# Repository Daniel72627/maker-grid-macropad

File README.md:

# The Maker Grid Macropad

The Maker Grid Macropad is a 9-key macropad with a rotary encoder and an OLED Display. It uses KMK firmware on a Seeed XIAO RP2040. 

It serves as a dedicated hardware tool to make designing custom robotics chassis, brackets, and mechanisms in CAD much more efficient!

## Features:
* 3D printed sandwich-style case. looks awesome doesn't it??
* 128x32 OLED Display to show active tool layers
* EC11 Rotary encoder for zooming and panning across the canvas
* 9 Keys for all my most-used CAD shortcuts

## CAD Model:

Everything fits together using M3 Bolts and heatset inserts. 
It has 2 separate 3D printed pieces. The bottom shell where the PCB sits, and the top plate with the cutouts for the switches. 

Made in Fusion360. Nifty

## PCB
Here's my PCB! It was made in KiCad. 

### Schematic

### PCB

I used a COL2ROW diode matrix for the keyswitch footprints to prevent ghosting. I think in retrospect, routing the I2C traces for the OLED was the trickiest part. 

## Firmware Overview
This hackpad uses KMK firmware (CircuitPython) for everything.

* The rotary encoder zooms in and out on the canvas. 
* The 9 keys currently act as macros for my most used Fusion 360 tools, dynamically changing based on whether I am Sketching, Solid Modeling, or Assembling.
* The OLED displays exactly which layer I am currently on!

I might add more in the future! That's it for now

## BOM:
Here should be everything you need to make this hackpad

* 9x Cherry MX-style Switches
* 9x Blank DSA Keycaps
* M3 Heat-Set Inserts & M3 Socket Cap Screws
* 9x 1N4148 Through-hole Diodes
* 1x 0.91" 128x32 OLED Display
* 1x EC11 Rotary Encoder + Knob
* 1x XIAO RP2040
* 1x Case (2 3D printed parts)

## Extra stuff
Oh fun fact: I designed this specifically because clicking through menus while designing our base robot for FTC Team 7082 was taking way too long LOL

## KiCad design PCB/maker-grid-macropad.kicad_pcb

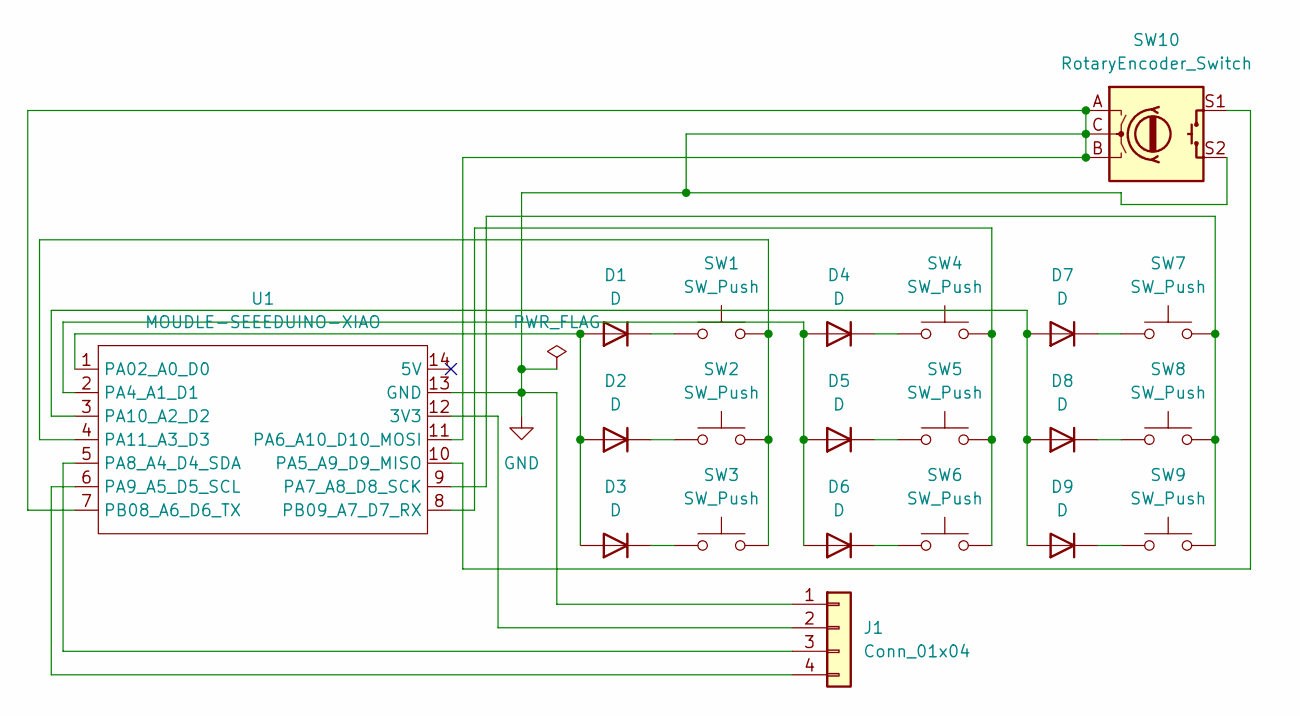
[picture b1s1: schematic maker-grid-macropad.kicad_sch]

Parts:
D1, D2, D3, D4, D5, D6, D7, D8, D9: D; D_DO-35_SOD27_P7.62mm_Horizontal
J1: Conn_01x04; PinHeader_1x04_P2.54mm_Vertical
SW1, SW2, SW3, SW4, SW5, SW6, SW7, SW8, SW9: SW_Push; SW_Cherry_MX_1.00u_PCB
SW10: RotaryEncoder_Switch; RotaryEncoder_Alps_EC11E-Switch_Vertical_H20mm
U1: MOUDLE-SEEEDUINO-XIAO; XIAO-Generic-Hybrid-14P-2.54-21X17.8MM

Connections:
GND: J1.1, SW10.A, SW10.B, SW10.C, SW10.S2, U1.7 (PB08_A6_D6_TX), U1.11 (PA6_A10_D10_MOSI), U1.13 (GND)
unnamed: D1.2 (A), D2.2 (A), D3.2 (A), U1.1 (PA02_A0_D0)
unnamed: D1.1 (K), SW1.1
unnamed: D2.1 (K), SW2.1
unnamed: D3.1 (K), SW3.1
unnamed: D4.2 (A), D5.2 (A), D6.2 (A), U1.2 (PA4_A1_D1)
unnamed: D4.1 (K), SW4.1
unnamed: D5.1 (K), SW5.1
unnamed: D6.1 (K), SW6.1
unnamed: D7.2 (A), D8.2 (A), D9.2 (A), U1.3 (PA10_A2_D2)
unnamed: D7.1 (K), SW7.1
unnamed: D8.1 (K), SW8.1
unnamed: D9.1 (K), SW9.1
unnamed: J1.2, U1.12 (3V3)
unnamed: J1.3, U1.5 (PA8_A4_D4_SDA)
unnamed: J1.4, U1.6 (PA9_A5_D5_SCL)
unnamed: SW10.S1, U1.10 (PA5_A9_D9_MISO)
unnamed: SW7.2, SW8.2, SW9.2, U1.9 (PA7_A8_D8_SCK)
unnamed: SW1.2, SW2.2, SW3.2, U1.4 (PA11_A3_D3)
unnamed: SW4.2, SW5.2, SW6.2, U1.8 (PB09_A7_D7_RX)

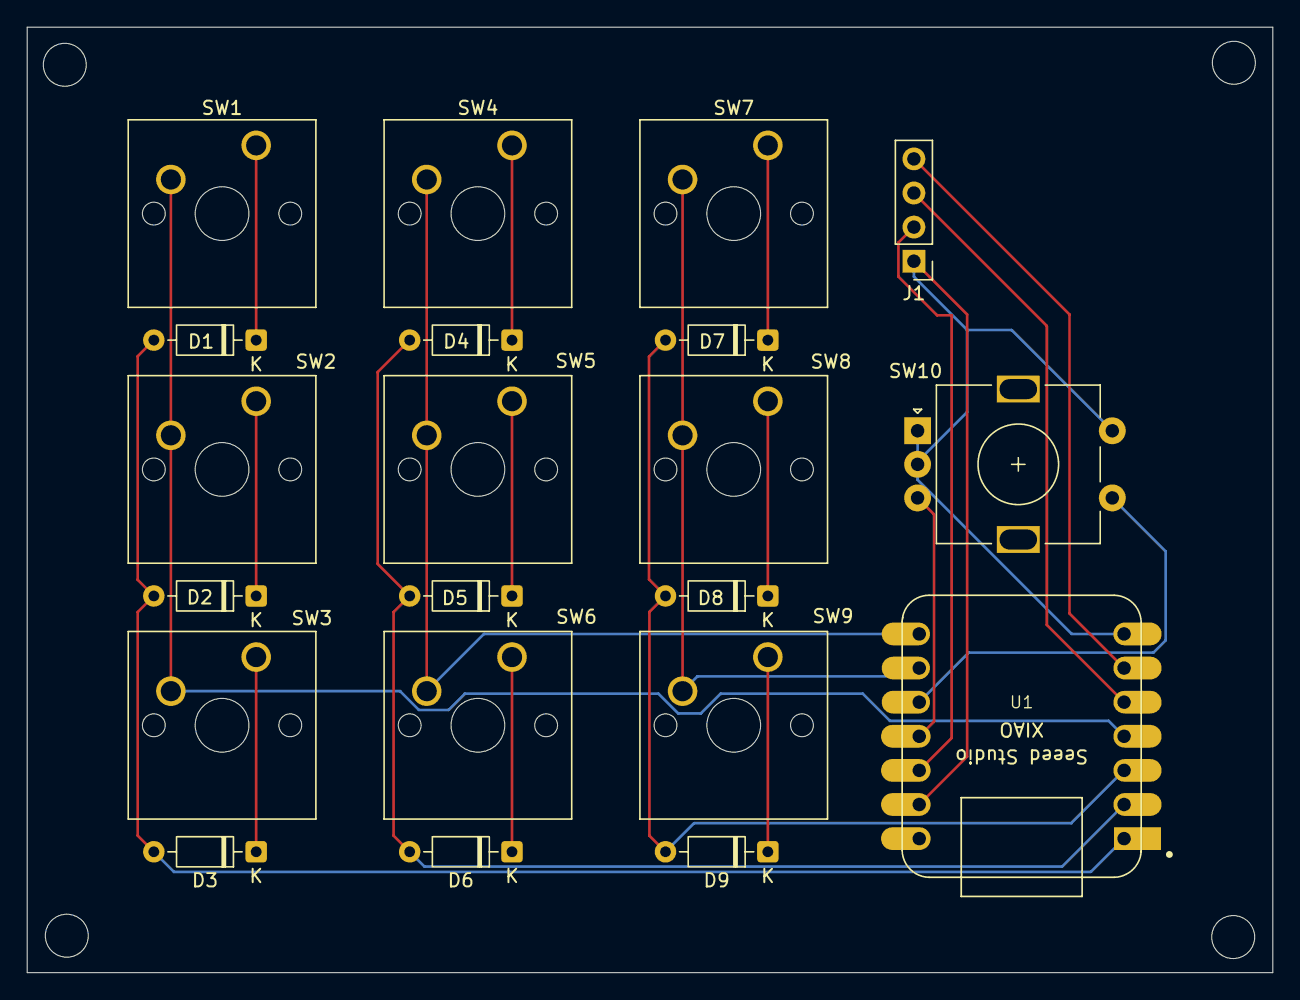
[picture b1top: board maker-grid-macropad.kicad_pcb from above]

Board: 2 copper layers, 92.7 x 70.4 mm, 21 parts (0 on the bottom side), 20 nets.

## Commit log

2026-06-23 Update README with macropad visuals and BOM
    Added images and information about the macropad, including schematics, PCB, case design, and Bill of Materials.
2026-06-23 v0.0
2026-06-26 v0.1
2026-06-26 v0.2
2026-06-26 v0.3
2026-06-26 v0.4
2026-06-26 v0.5
2026-06-30 v1.0
2026-06-30 v1.1
2026-06-30 v1.2 (Final Commit)
